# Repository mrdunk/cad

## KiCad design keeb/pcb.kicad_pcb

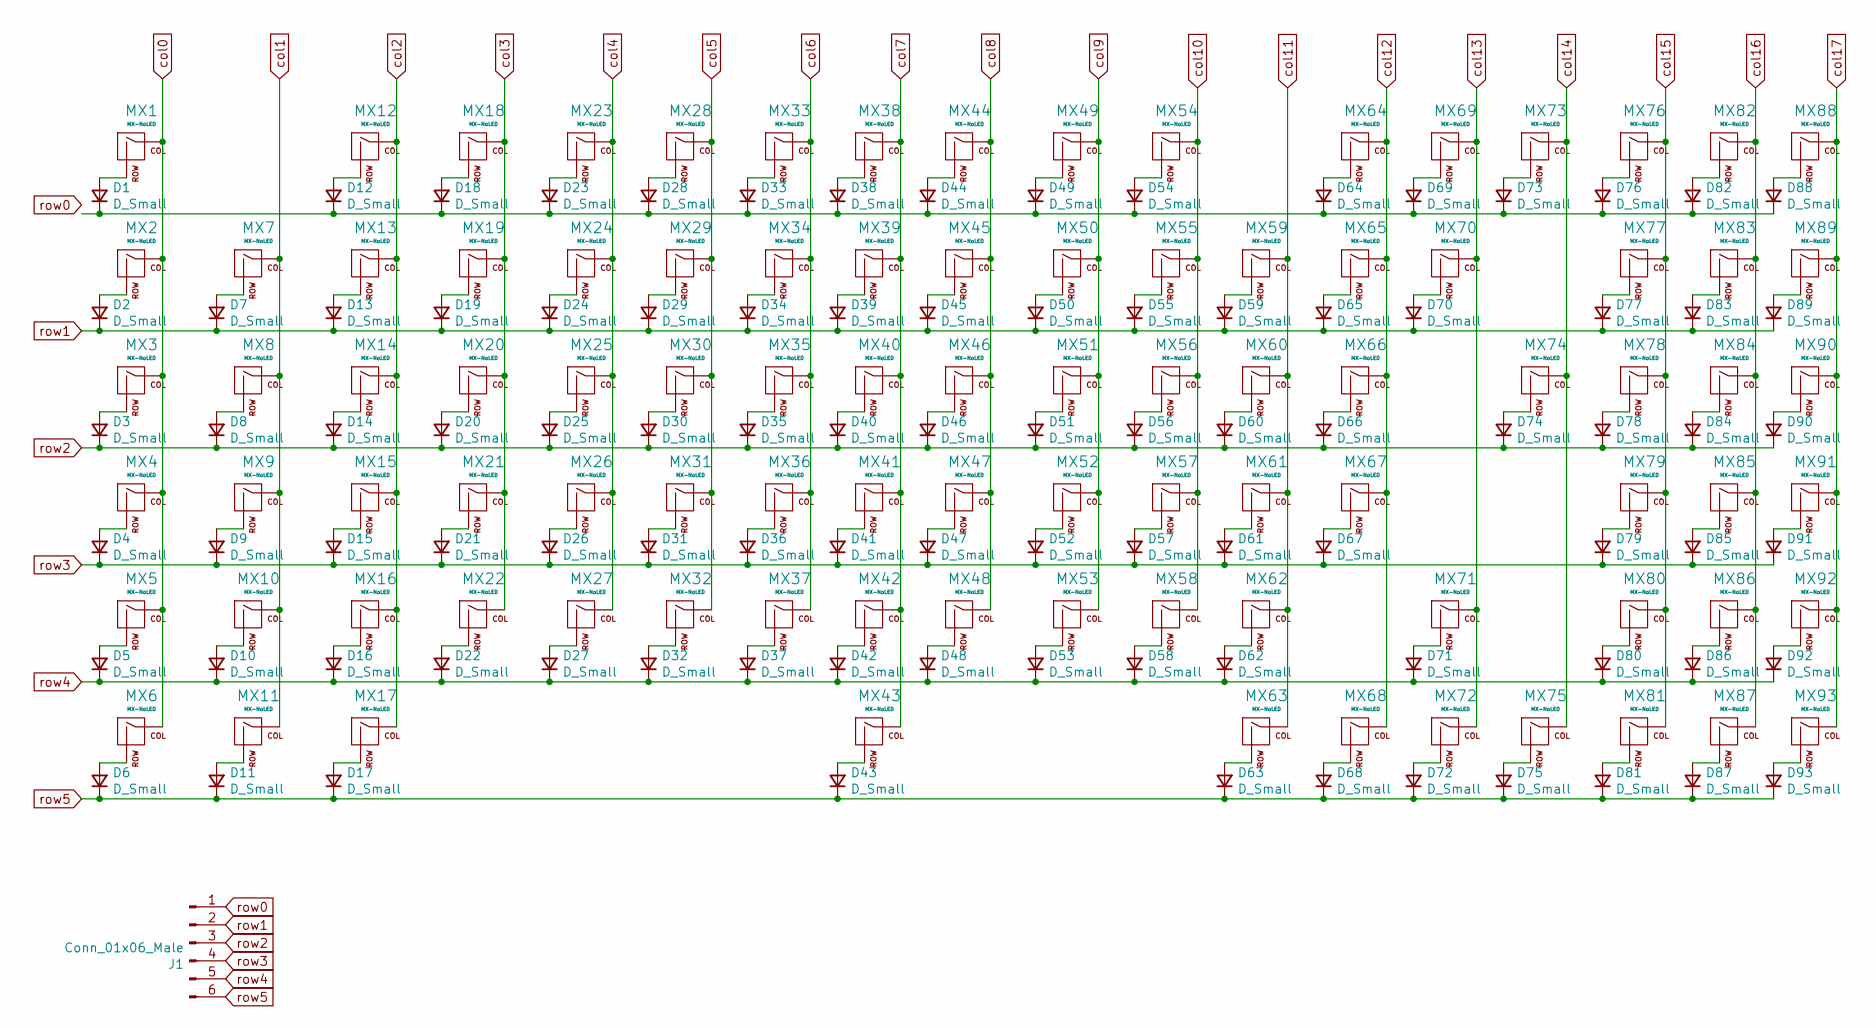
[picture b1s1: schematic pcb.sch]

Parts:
D1, D2, D3, D4, D5, D6, D7, D8, D9, D10, D11, D12, D13, D14, D15, D16, D17, D18, D19, D20, D21, D22, D23, D24, D25, D26, D27, D28, D29, D30, D31, D32, D33, D34, D35, D36, D37, D38, D39, D40, D41, D42, D43, D44, D45, D46, D47, D48, D49, D50, D51, D52, D53, D54, D55, D56, D57, D58, D59, D60, D61, D62, D63, D64, D65, D66, D67, D68, D69, D70, D71, D72, D73, D74, D75, D76, D77, D78, D79, D80, D81, D82, D83, D84, D85, D86, D87, D88, D89, D90, D91, D92, D93: D_Small; D_DO-27_P12.70mm_Horizontal
J1: Conn_01x06_Male; PinHeader_1x06_P1.27mm_Horizontal
MX1, MX2, MX7, MX8, MX9, MX10, MX12, MX13, MX14, MX15, MX16, MX18, MX19, MX20, MX21, MX22, MX23, MX24, MX25, MX26, MX27, MX28, MX29, MX30, MX31, MX32, MX33, MX34, MX35, MX36, MX37, MX38, MX39, MX40, MX41, MX42, MX44, MX45, MX46, MX47, MX48, MX49, MX50, MX51, MX52, MX53, MX54, MX55, MX56, MX57, MX58, MX59, MX60, MX61, MX62, MX64, MX65, MX66, MX67, MX69, MX73, MX76, MX77, MX78, MX79, MX80, MX81, MX82, MX83, MX84, MX85, MX86, MX87, MX88, MX89, MX90, MX91, MX92, MX93: MX-NoLED; MXOnly-1U
MX3: MX-NoLED; MXOnly-1.5U
MX4: MX-NoLED; MXOnly-1.75U
MX5, MX6, MX11, MX17, MX63, MX68, MX72, MX75: MX-NoLED; MXOnly-1.25U
MX43: MX-NoLED; MXOnly-6.25U
MX70: MX-NoLED; MXOnly-2U
MX71: MX-NoLED; MXOnly-2.75U
MX74: MX-NoLED; MXOnly-ISO

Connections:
unnamed 0: D1.1 (K), D12.1 (K), D18.1 (K), D23.1 (K), D28.1 (K), D33.1 (K), D38.1 (K), D44.1 (K), D49.1 (K), D54.1 (K), D64.1 (K), D69.1 (K), D73.1 (K), D76.1 (K), D82.1 (K), D88.1 (K); also elsewhere on the board
unnamed: D1.2 (A), MX1.2 (ROW)
unnamed: D2.2 (A), MX2.2 (ROW)
unnamed: D3.2 (A), MX3.2 (ROW)
unnamed: D4.2 (A), MX4.2 (ROW)
unnamed: D5.2 (A), MX5.2 (ROW)
unnamed: D6.2 (A), MX6.2 (ROW)
unnamed: D7.2 (A), MX7.2 (ROW)
unnamed: D8.2 (A), MX8.2 (ROW)
unnamed: D9.2 (A), MX9.2 (ROW)
unnamed: D10.2 (A), MX10.2 (ROW)
unnamed: D11.2 (A), MX11.2 (ROW)
unnamed: D12.2 (A), MX12.2 (ROW)
unnamed: D13.2 (A), MX13.2 (ROW)
unnamed: D14.2 (A), MX14.2 (ROW)
unnamed: D15.2 (A), MX15.2 (ROW)
unnamed: D16.2 (A), MX16.2 (ROW)
unnamed: D17.2 (A), MX17.2 (ROW)
unnamed: D18.2 (A), MX18.2 (ROW)
unnamed: D19.2 (A), MX19.2 (ROW)
unnamed: D20.2 (A), MX20.2 (ROW)
unnamed: D21.2 (A), MX21.2 (ROW)
unnamed: D22.2 (A), MX22.2 (ROW)
unnamed: D23.2 (A), MX23.2 (ROW)
unnamed: D24.2 (A), MX24.2 (ROW)
unnamed: D25.2 (A), MX25.2 (ROW)
unnamed: D26.2 (A), MX26.2 (ROW)
unnamed: D27.2 (A), MX27.2 (ROW)
unnamed: D28.2 (A), MX28.2 (ROW)
unnamed: D29.2 (A), MX29.2 (ROW)
unnamed: D30.2 (A), MX30.2 (ROW)
unnamed: D31.2 (A), MX31.2 (ROW)
unnamed: D32.2 (A), MX32.2 (ROW)
unnamed: D33.2 (A), MX33.2 (ROW)
unnamed: D34.2 (A), MX34.2 (ROW)
unnamed: D35.2 (A), MX35.2 (ROW)
unnamed: D36.2 (A), MX36.2 (ROW)
unnamed: D37.2 (A), MX37.2 (ROW)
unnamed: D38.2 (A), MX38.2 (ROW)
unnamed: D39.2 (A), MX39.2 (ROW)
unnamed: D40.2 (A), MX40.2 (ROW)
unnamed: D41.2 (A), MX41.2 (ROW)
unnamed: D42.2 (A), MX42.2 (ROW)
unnamed: D43.2 (A), MX43.2 (ROW)
unnamed: D44.2 (A), MX44.2 (ROW)
unnamed: D45.2 (A), MX45.2 (ROW)
unnamed: D46.2 (A), MX46.2 (ROW)
unnamed: D47.2 (A), MX47.2 (ROW)
unnamed: D48.2 (A), MX48.2 (ROW)
unnamed: D49.2 (A), MX49.2 (ROW)
unnamed: D50.2 (A), MX50.2 (ROW)
unnamed: D51.2 (A), MX51.2 (ROW)
unnamed: D52.2 (A), MX52.2 (ROW)
unnamed: D53.2 (A), MX53.2 (ROW)
unnamed: D54.2 (A), MX54.2 (ROW)
unnamed: D55.2 (A), MX55.2 (ROW)
unnamed: D56.2 (A), MX56.2 (ROW)
unnamed: D57.2 (A), MX57.2 (ROW)
unnamed: D58.2 (A), MX58.2 (ROW)
unnamed: D59.2 (A), MX59.2 (ROW)
unnamed: D60.2 (A), MX60.2 (ROW)
unnamed: D61.2 (A), MX61.2 (ROW)
unnamed: D62.2 (A), MX62.2 (ROW)
unnamed: D63.2 (A), MX63.2 (ROW)
unnamed: D64.2 (A), MX64.2 (ROW)
unnamed: D65.2 (A), MX65.2 (ROW)
unnamed: D66.2 (A), MX66.2 (ROW)
unnamed: D67.2 (A), MX67.2 (ROW)
unnamed: D68.2 (A), MX68.2 (ROW)
unnamed: D69.2 (A), MX69.2 (ROW)
unnamed: D70.2 (A), MX70.2 (ROW)
unnamed: D71.2 (A), MX71.2 (ROW)
unnamed: D72.2 (A), MX72.2 (ROW)
unnamed: D73.2 (A), MX73.2 (ROW)
unnamed: D74.2 (A), MX74.2 (ROW)
unnamed: D75.2 (A), MX75.2 (ROW)
unnamed: D76.2 (A), MX76.2 (ROW)
unnamed: D77.2 (A), MX77.2 (ROW)
unnamed: D78.2 (A), MX78.2 (ROW)
unnamed: D79.2 (A), MX79.2 (ROW)
unnamed: D80.2 (A), MX80.2 (ROW)
unnamed: D81.2 (A), MX81.2 (ROW)
unnamed: D82.2 (A), MX82.2 (ROW)
unnamed: D83.2 (A), MX83.2 (ROW)
unnamed: D84.2 (A), MX84.2 (ROW)
unnamed: D85.2 (A), MX85.2 (ROW)
unnamed: D86.2 (A), MX86.2 (ROW)
unnamed: D87.2 (A), MX87.2 (ROW)
unnamed: D88.2 (A), MX88.2 (ROW)
unnamed: D89.2 (A), MX89.2 (ROW)
unnamed: D90.2 (A), MX90.2 (ROW)
unnamed: D91.2 (A), MX91.2 (ROW)
unnamed: D92.2 (A), MX92.2 (ROW)
unnamed: D93.2 (A), MX93.2 (ROW)
col0: MX1.1 (COL), MX2.1 (COL), MX3.1 (COL), MX4.1 (COL), MX5.1 (COL), MX6.1 (COL); also elsewhere on the board
col1: MX7.1 (COL), MX8.1 (COL), MX9.1 (COL), MX10.1 (COL), MX11.1 (COL); also elsewhere on the board
col2: MX12.1 (COL), MX13.1 (COL), MX14.1 (COL), MX15.1 (COL), MX16.1 (COL), MX17.1 (COL); also elsewhere on the board
col3: MX18.1 (COL), MX19.1 (COL), MX20.1 (COL), MX21.1 (COL), MX22.1 (COL); also elsewhere on the board
col4: MX23.1 (COL), MX24.1 (COL), MX25.1 (COL), MX26.1 (COL), MX27.1 (COL); also elsewhere on the board
col5: MX28.1 (COL), MX29.1 (COL), MX30.1 (COL), MX31.1 (COL), MX32.1 (COL); also elsewhere on the board
col6: MX33.1 (COL), MX34.1 (COL), MX35.1 (COL), MX36.1 (COL), MX37.1 (COL); also elsewhere on the board
col7: MX38.1 (COL), MX39.1 (COL), MX40.1 (COL), MX41.1 (COL), MX42.1 (COL), MX43.1 (COL); also elsewhere on the board
col8: MX44.1 (COL), MX45.1 (COL), MX46.1 (COL), MX47.1 (COL), MX48.1 (COL); also elsewhere on the board
col9: MX49.1 (COL), MX50.1 (COL), MX51.1 (COL), MX52.1 (COL), MX53.1 (COL); also elsewhere on the board
col10: MX54.1 (COL), MX55.1 (COL), MX56.1 (COL), MX57.1 (COL), MX58.1 (COL); also elsewhere on the board
col11: MX59.1 (COL), MX60.1 (COL), MX61.1 (COL), MX62.1 (COL), MX63.1 (COL); also elsewhere on the board
col12: MX64.1 (COL), MX65.1 (COL), MX66.1 (COL), MX67.1 (COL), MX68.1 (COL); also elsewhere on the board
col13: MX69.1 (COL), MX70.1 (COL), MX71.1 (COL), MX72.1 (COL); also elsewhere on the board
col14: MX73.1 (COL), MX74.1 (COL), MX75.1 (COL); also elsewhere on the board
col15: MX76.1 (COL), MX77.1 (COL), MX78.1 (COL), MX79.1 (COL), MX80.1 (COL), MX81.1 (COL); also elsewhere on the board
col16: MX82.1 (COL), MX83.1 (COL), MX84.1 (COL), MX85.1 (COL), MX86.1 (COL), MX87.1 (COL); also elsewhere on the board
col17: MX88.1 (COL), MX89.1 (COL), MX90.1 (COL), MX91.1 (COL), MX92.1 (COL), MX93.1 (COL); also elsewhere on the board
row0: J1.1
row1: D2.1 (K), D7.1 (K), D13.1 (K), D19.1 (K), D24.1 (K), D29.1 (K), D34.1 (K), D39.1 (K), D45.1 (K), D50.1 (K), D55.1 (K), D59.1 (K), D65.1 (K), D70.1 (K), D77.1 (K), D83.1 (K), D89.1 (K), J1.2; also elsewhere on the board
row2: D3.1 (K), D8.1 (K), D14.1 (K), D20.1 (K), D25.1 (K), D30.1 (K), D35.1 (K), D40.1 (K), D46.1 (K), D51.1 (K), D56.1 (K), D60.1 (K), D66.1 (K), D74.1 (K), D78.1 (K), D84.1 (K), D90.1 (K), J1.3; also elsewhere on the board
row3: D4.1 (K), D9.1 (K), D15.1 (K), D21.1 (K), D26.1 (K), D31.1 (K), D36.1 (K), D41.1 (K), D47.1 (K), D52.1 (K), D57.1 (K), D61.1 (K), D67.1 (K), D79.1 (K), D85.1 (K), D91.1 (K), J1.4; also elsewhere on the board
row4: D5.1 (K), D10.1 (K), D16.1 (K), D22.1 (K), D27.1 (K), D32.1 (K), D37.1 (K), D42.1 (K), D48.1 (K), D53.1 (K), D58.1 (K), D62.1 (K), D71.1 (K), D80.1 (K), D86.1 (K), D92.1 (K), J1.5; also elsewhere on the board
row5: D6.1 (K), D11.1 (K), D17.1 (K), D43.1 (K), D63.1 (K), D68.1 (K), D72.1 (K), D75.1 (K), D81.1 (K), D87.1 (K), D93.1 (K), J1.6; also elsewhere on the board

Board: 2 copper layers, 200 parts (0 on the bottom side), 124 nets, no tracks yet.

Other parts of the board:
D94, D95, D96, D97, D98, D99: D_Small; D_DO-27_P12.70mm_Horizontal
J2: Conn_01x19_Male; PinHeader_1x19_P1.27mm_Horizontal
MX94, MX95, MX96, MX97, MX98, MX99: MX-NoLED; MXOnly-1U

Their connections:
unnamed 0: D94.1; also elsewhere on the board
unnamed: D94.2, MX94.2
unnamed: D95.2, MX95.2
unnamed: D96.2, MX96.2
unnamed: D97.2, MX97.2
unnamed: D98.2, MX98.2
unnamed: D99.2, MX99.2
col0: J2.1; also elsewhere on the board
col1: J2.2; also elsewhere on the board
col2: J2.3; also elsewhere on the board
col3: J2.4; also elsewhere on the board
col4: J2.5; also elsewhere on the board
col5: J2.6; also elsewhere on the board
col6: J2.7; also elsewhere on the board
col7: J2.8; also elsewhere on the board
col8: J2.9; also elsewhere on the board
col9: J2.10; also elsewhere on the board
col10: J2.11; also elsewhere on the board
col11: J2.12; also elsewhere on the board
col12: J2.13; also elsewhere on the board
col13: J2.14; also elsewhere on the board
col14: J2.15; also elsewhere on the board
col15: J2.16; also elsewhere on the board
col16: J2.17; also elsewhere on the board
col17: J2.18; also elsewhere on the board
col18: J2.19, MX94.1, MX95.1, MX96.1, MX97.1, MX98.1, MX99.1
row1: D95.1; also elsewhere on the board
row2: D96.1; also elsewhere on the board
row3: D97.1; also elsewhere on the board
row4: D98.1; also elsewhere on the board
row5: D99.1; also elsewhere on the board

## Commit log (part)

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2022-05-04 Add sliding doors.
2022-05-04 brake gap in backboard.
2022-05-05 left/right.
2022-05-13 Add lense drawing script
2022-06-22 Keyboard files.
2022-11-02 various files from the last few months.
2023-02-03 various lathe bits
2024-03-14 various 2023 - march 2024.
2024-09-13 various ongoing updates.
